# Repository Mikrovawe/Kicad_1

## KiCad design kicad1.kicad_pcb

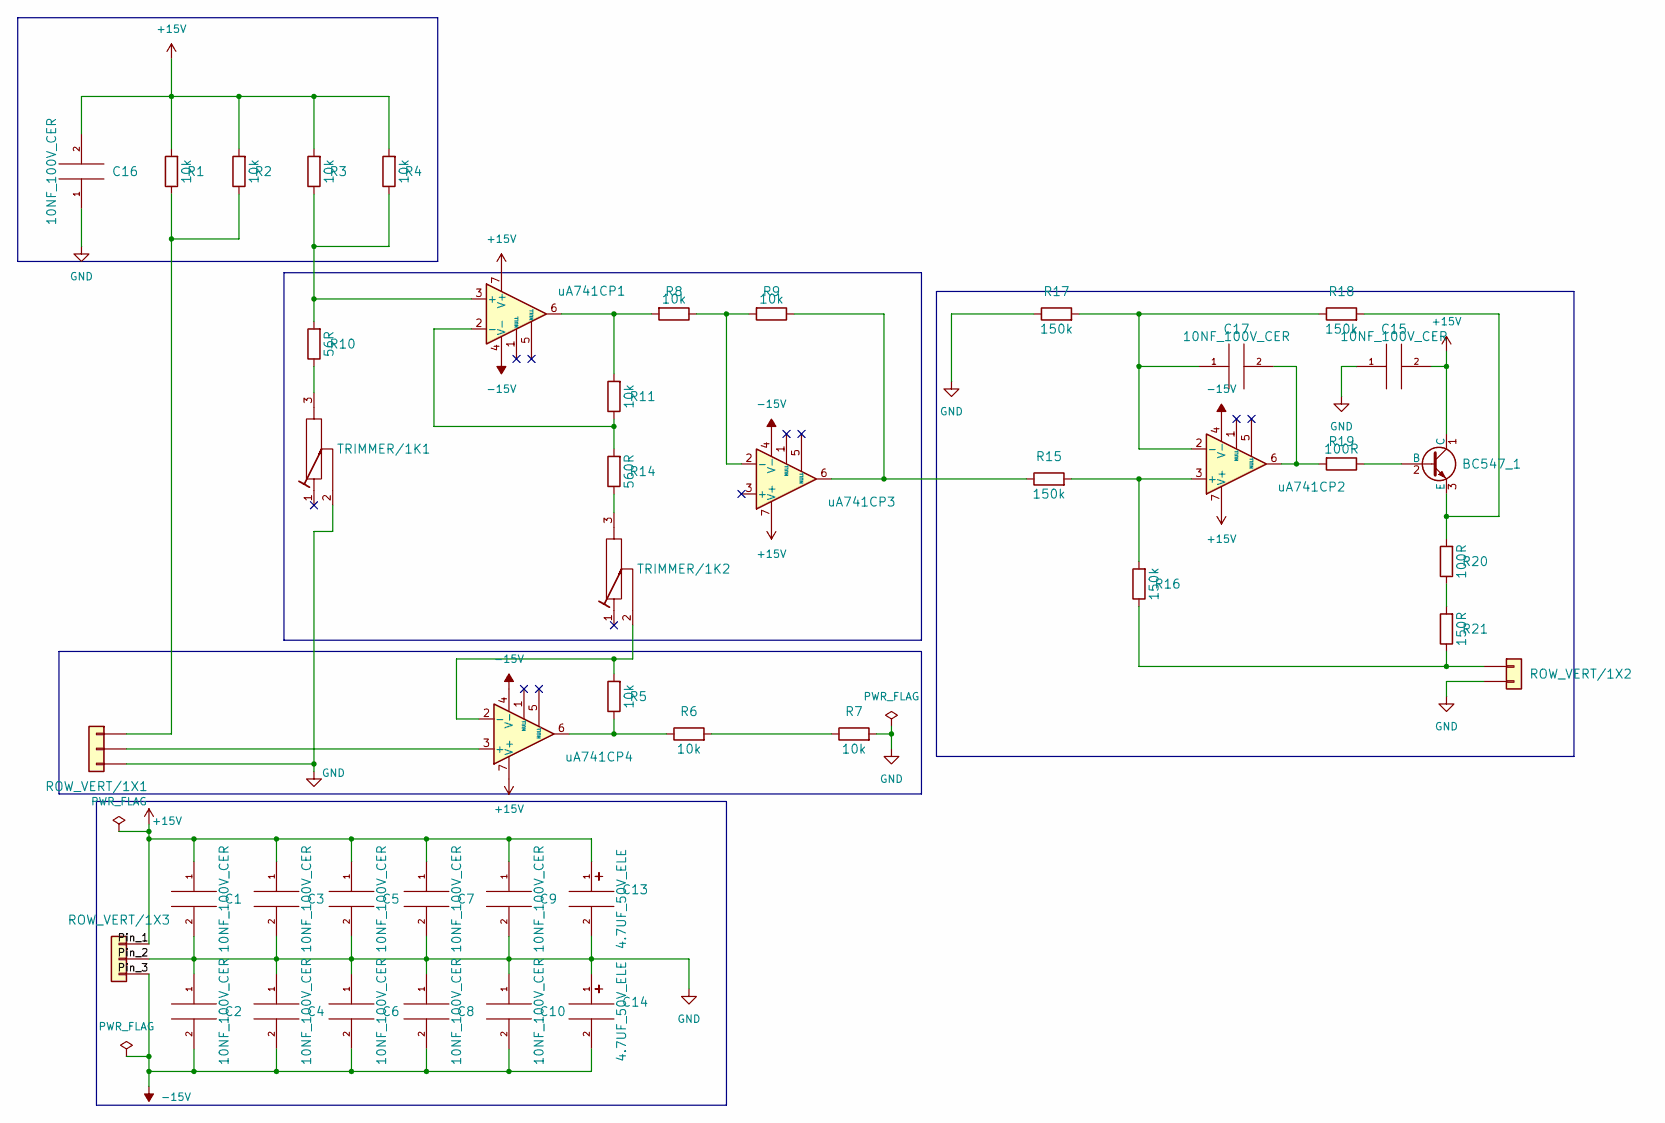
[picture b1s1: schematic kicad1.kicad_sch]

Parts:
BC547_1: BC547_TO92_0.1A; TO-92
C1, C2, C3, C4, C5, C6, C7, C8, C9, C10, C15, C16, C17: 10NF_100V_CER; C5_0; Tolerance +-10%
C13, C14: 4.7UF_50V_ELE; C_P_2_0_5; Tolerance +-20%
R1, R2, R3, R4, R5, R6, R7, R8, R9, R11: 10k; R3_5W; Tolerance +-1%
R10: 56R; R3_5W; Tolerance +-1%
R14: 560R; R3_5W; Tolerance +-1%
R15, R16, R17, R18: 150k; R3_5W; Tolerance +-1%
R19, R20: 100R; R3_5W; Tolerance +-1%
R21: 150R; R3_5W; Tolerance +-1%
ROW_VERT/1X1, ROW_VERT/1X3: ROW_VERT_1X3; ROW_VERT_1x3
ROW_VERT/1X2: ROW_VERT_1X2; ROW_VERT_1x2
TRIMMER/1K1, TRIMMER/1K2: TRIMMER_1K; TRIMMER
uA741CP1, uA741CP2, uA741CP3, uA741CP4: uA741CP_DIL8; DIL8

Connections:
+15V: BC547_1.1 (C), C1.1, C3.1, C5.1, C7.1, C9.1, C13.1, C15.2, C16.2, R1.2, R2.2, R3.2, R4.2, ROW_VERT/1X3.1, uA741CP1.7 (V+), uA741CP2.7 (V+), uA741CP3.7 (V+), uA741CP4.7 (V+)
-15V: C2.2, C4.2, C6.2, C8.2, C10.2, C14.2, ROW_VERT/1X3.3, uA741CP1.4 (V-), uA741CP2.4 (V-), uA741CP3.4 (V-), uA741CP4.4 (V-)
GND: C1.2, C2.1, C3.2, C4.1, C5.2, C6.1, C7.2, C8.1, C9.2, C10.1, C13.2, C14.1, C15.1, C16.1, R7.2, R17.1, ROW_VERT/1X1.3, ROW_VERT/1X2.2, ROW_VERT/1X3.2, TRIMMER/1K1.2
unnamed: BC547_1.2 (B), R19.1
unnamed: BC547_1.3 (E), R18.2, R20.2
unnamed: C17.2, R19.2, uA741CP2.6
unnamed: R5.1, R6.1, uA741CP4.6
unnamed: R6.2, R7.1
unnamed: R10.1, TRIMMER/1K1.3
unnamed: R8.2, R11.2, uA741CP1.6
unnamed: R14.1, TRIMMER/1K2.3
unnamed: R9.1, R15.1, uA741CP3.6
unnamed: R20.1, R21.2
unnamed: R1.1, R2.1, ROW_VERT/1X1.1
unnamed: ROW_VERT/1X1.2, uA741CP4.3 (+)
unnamed: R16.1, R21.1, ROW_VERT/1X2.1
unnamed: R3.1, R4.1, R10.2, uA741CP1.3 (+)
unnamed: R11.1, R14.2, uA741CP1.2 (-)
unnamed: R15.2, R16.2, uA741CP2.3 (+)
unnamed: C17.1, R17.2, R18.1, uA741CP2.2 (-)
unnamed: R8.1, R9.2, uA741CP3.2 (-)
unnamed: R5.2, TRIMMER/1K2.2, uA741CP4.2 (-)

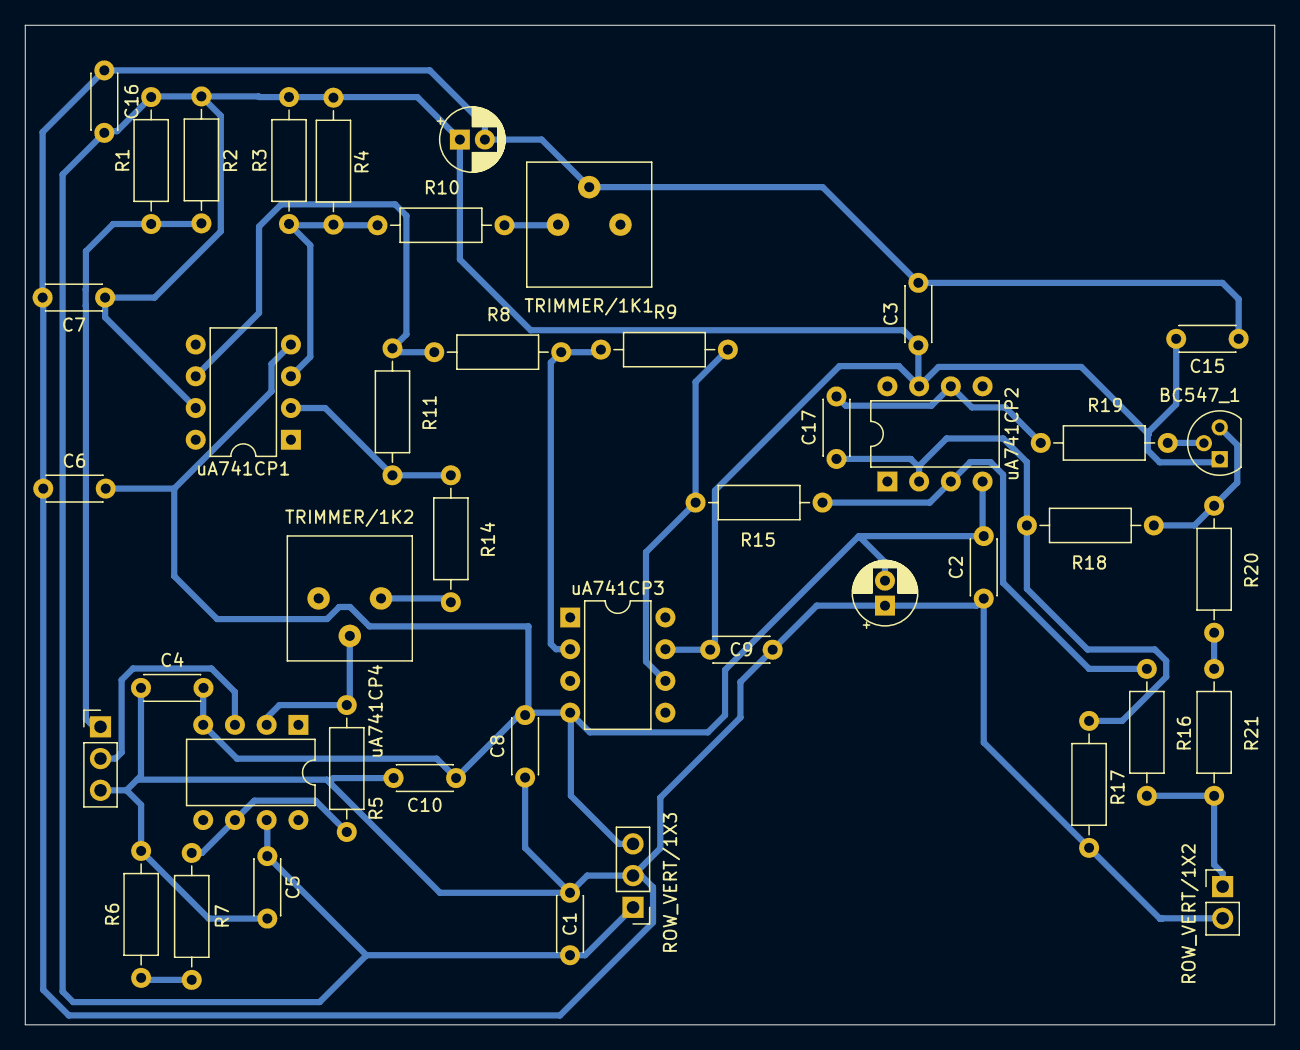
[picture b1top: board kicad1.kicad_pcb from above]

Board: 2 copper layers, 100.0 x 80.0 mm, 44 parts (0 on the bottom side), 22 nets.

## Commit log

2026-01-27 initial KiCad project
2026-01-27 An abomination of a first version
2026-02-02 pusku
2026-02-02 epätoivoinen versio ennen resettiä
2026-02-02 done
